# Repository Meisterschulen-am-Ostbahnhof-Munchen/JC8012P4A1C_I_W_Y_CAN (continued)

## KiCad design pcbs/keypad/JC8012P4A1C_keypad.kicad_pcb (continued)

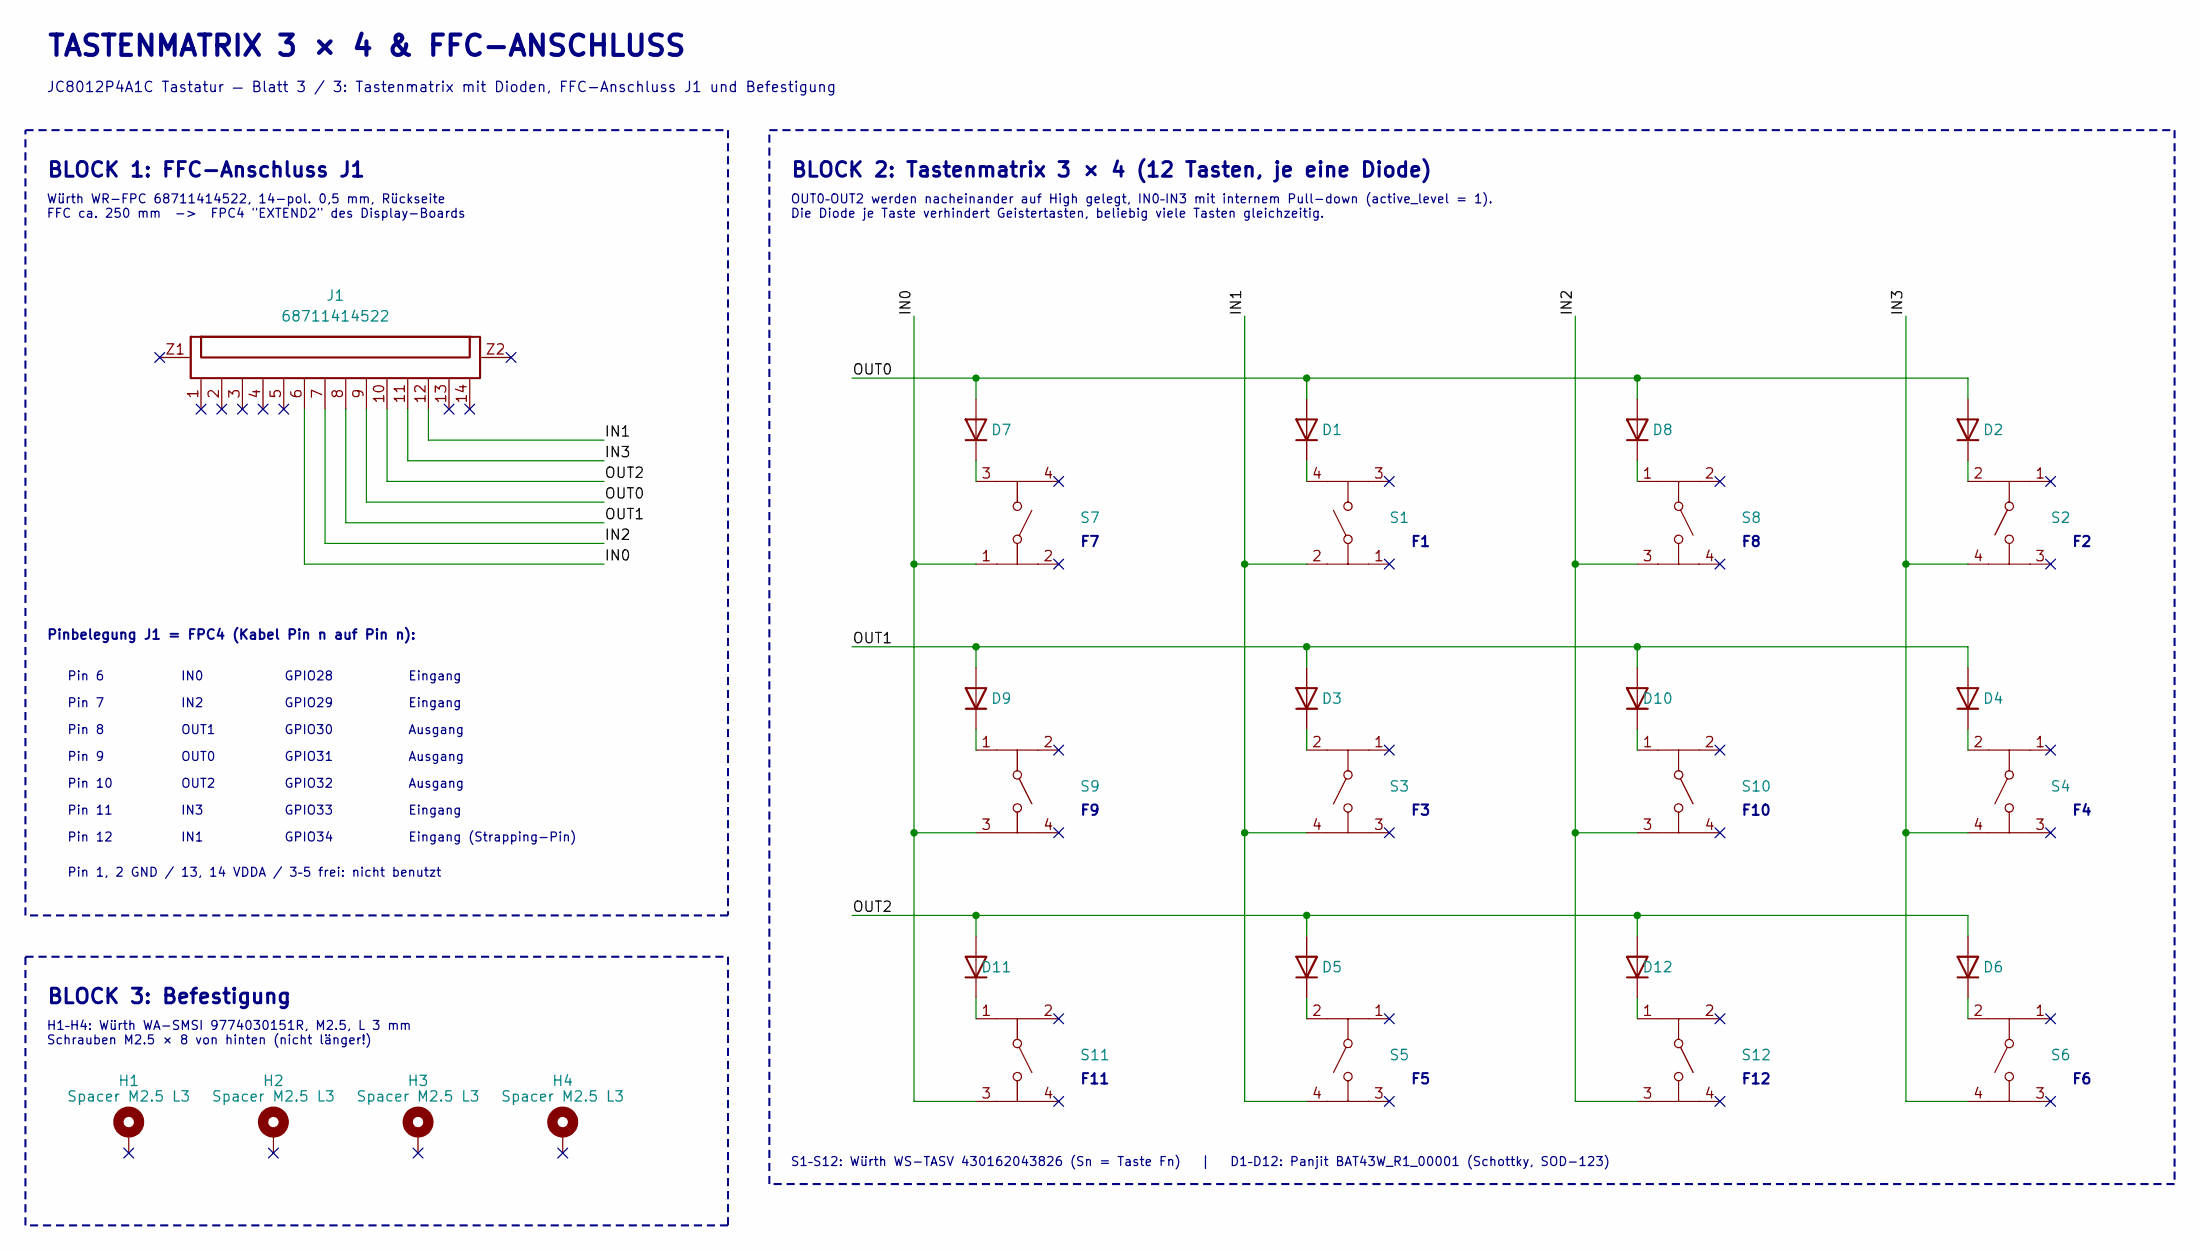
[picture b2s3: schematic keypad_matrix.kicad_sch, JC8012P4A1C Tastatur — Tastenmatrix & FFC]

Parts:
D1, D2, D3, D4, D5, D6, D7, D8, D9, D10, D11, D12: BAT43W; D_SOD-123; MPN BAT43W_R1_00001
H1, H2, H3, H4: Spacer M2.5 L3; A_Wurth_WA-SMSI_9774030151R; MPN 9774030151R
J1: 68711414522; J_Wurth_WR-FPC_68711414522; MPN 68711414522
S1, S2, S3, S4, S5, S6, S7, S8, S9, S10, S11, S12: 430162043826; SW_Wurth_WS-TASV_430162043826; MPN 430162043826

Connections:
/Tastenmatrix/IN0: J1.6, S7.1, S9.3, S11.3
/Tastenmatrix/IN1: J1.12, S1.2, S3.4, S5.4
/Tastenmatrix/IN2: J1.7, S8.3, S10.3, S12.3
/Tastenmatrix/IN3: J1.11, S2.4, S4.4, S6.4
/Tastenmatrix/OUT0: D1.2 (A), D2.2 (A), D7.2 (A), D8.2 (A), J1.9
/Tastenmatrix/OUT1: D3.2 (A), D4.2 (A), D9.2 (A), D10.2 (A), J1.8
/Tastenmatrix/OUT2: D5.2 (A), D6.2 (A), D11.2 (A), D12.2 (A), J1.10
unnamed: D1.1 (K), S1.4
unnamed: D2.1 (K), S2.2
unnamed: D3.1 (K), S3.2
unnamed: D4.1 (K), S4.2
unnamed: D5.1 (K), S5.2
unnamed: D6.1 (K), S6.2
unnamed: D7.1 (K), S7.3
unnamed: D8.1 (K), S8.1
unnamed: D9.1 (K), S9.1
unnamed: D10.1 (K), S10.1
unnamed: D11.1 (K), S11.1
unnamed: D12.1 (K), S12.1

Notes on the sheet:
GPIO29
Ausgang
BLOCK 2: Tastenmatrix 3 × 4 (12 Tasten, je eine Diode)
GPIO31
BLOCK 3: Befestigung
Pin 6
F10
OUT0
Pin 10
GPIO33
H1–H4: Würth WA-SMSI 9774030151R, M2.5, L 3 mm Schrauben M2.5 × 8 von hinten (nicht länger!)
Eingang (Strapping-Pin)
GPIO30
Eingang
GPIO32
GPIO28
IN1
Pin 12
OUT2
Pinbelegung J1 = FPC4 (Kabel Pin n auf Pin n):
Pin 8
GPIO34
F11
Pin 1, 2 GND / 13, 14 VDDA / 3–5 frei: nicht benutzt
BLOCK 1: FFC-Anschluss J1
Würth WR-FPC 68711414522, 14-pol. 0,5 mm, Rückseite FFC ca. 250 mm -> FPC4 "EXTEND2" des Display-Boards
IN3
IN2
Pin 9
Pin 11
Pin 7
OUT1
OUT0–OUT2 werden nacheinander auf High gelegt, IN0–IN3 mit internem Pull-down (active_level = 1). Die Diode je Taste verhindert Geistertasten, beliebig viele Tasten gleichzeitig.
IN0
JC8012P4A1C Tastatur — Blatt 3 / 3: Tastenmatrix mit Dioden, FFC-Anschluss J1 und Befestigung
TASTENMATRIX 3 × 4 & FFC-ANSCHLUSS
F12
S1–S12: Würth WS-TASV 430162043826 (Sn = Taste Fn) | D1–D12: Panjit BAT43W_R1_00001 (Schottky, SOD-123)

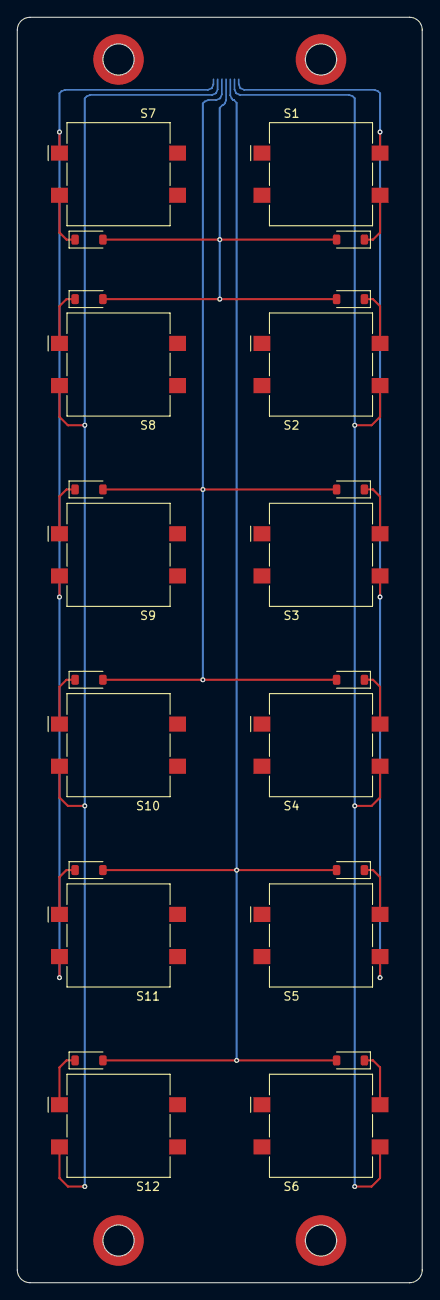
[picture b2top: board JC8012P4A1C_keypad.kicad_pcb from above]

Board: 2 copper layers, 48.0 x 150.0 mm, 29 parts (1 on the bottom side), 19 nets.
